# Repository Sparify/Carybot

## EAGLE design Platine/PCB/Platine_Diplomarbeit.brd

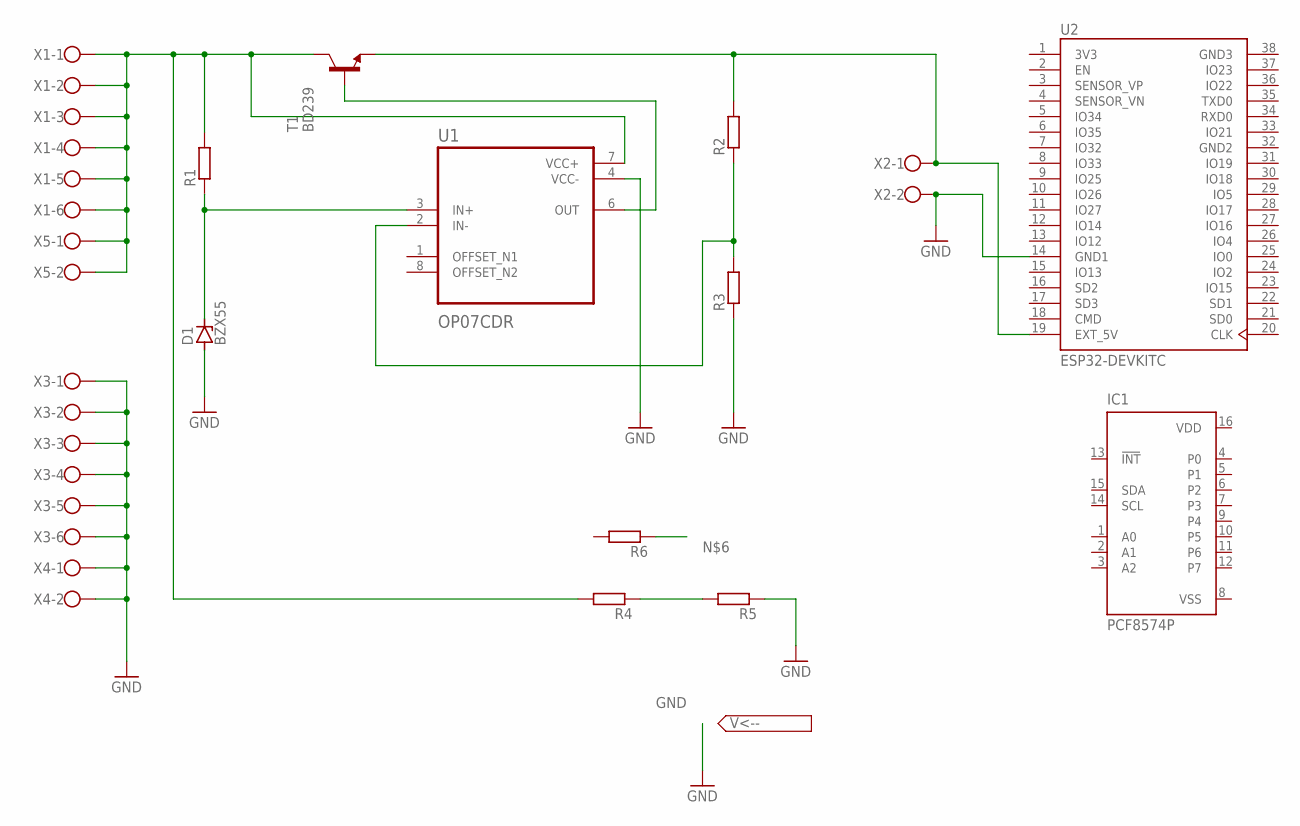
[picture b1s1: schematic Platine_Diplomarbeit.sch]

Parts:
D1: BZX55; DO35Z10
IC1: PCF8574P; DIL16
R1, R2, R3, R4, R5, R6: R-EU_0309/12; 0309/12
T1: BD239; TO220
U1: OP07CDR; SOIC127P599X175-8N
U2: ESP32-DEVKITC; MODULE_ESP32-DEVKITC
X1, X3: W237-6
X2, X4, X5: W237-102

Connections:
3V3: U2.1 (3V3)
GND: D1.A, R3.1, R5.1, U1.4 (VCC-), U2.14 (GND1), X2.2, X3.1, X3.2, X3.3, X3.4, X3.5, X3.6, X4.1, X4.2
GND1: R1.2, R4.2, T1.2 (C), U1.7 (VCC+), X1.1, X1.2, X1.3, X1.4, X1.5, X1.6, X5.1, X5.2
GND2: U2.32 (GND2)
GND3: U2.38 (GND3)
unnamed: D1.C, R1.1, U1.3 (IN+)
unnamed: R4.1, R5.2
unnamed: R2.2, T1.3 (E), U2.19 (EXT_5V), X2.1
unnamed: R2.1, R3.2, U1.2 (IN-)
unnamed: T1.1 (B), U1.6 (OUT)
VDD: IC1.16 (VDD)
VSS: IC1.8 (VSS)

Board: 2 copper layers, 16 parts (0 on the bottom side), 7 nets, no tracks yet.

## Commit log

2024-11-07 steuerung für 2 motoren
2024-11-07 Webserver files upload
2024-11-13 camera buttons + menu
2024-11-13 external files for js and css
2024-11-14 add 2nd site + cam_controll HTTPRequest + external files for css & js
2024-11-14 activate video stream
2024-11-14 add toggleable menu
2024-11-15 fixing body border
2024-11-20 change data from external site to menu
2024-11-21 remove RSSI & unused css
2024-12-06 Steuerungsoptimierung
2024-12-12 Change from HTTP to Websockets
2024-12-12 Webservercodeoptimierung
2024-12-19 Adding anti select + fixing cam control
2024-12-19 Codeoptimierung
2024-12-19 Codeoptimierungen
2024-12-28 Add files via upload
    v2
2024-12-28 Steuerung für 4 Motoren
2025-01-04 add connection status box
2025-01-04 fix control issue
2025-01-08 Spannungs_Messung
2025-01-09 distancesensor + spannungsmessung
2025-01-16 Akkustand auf webserver übertragen
2025-01-22 Change Host to ESP-CAM
2025-01-26 Videoübertragung über Websockets
2025-01-27 full websocket communication
2025-01-27 motorsteuerung implementieren
2025-01-27 improve fps + akkustand übertragen
2025-01-27 eigenes netzwerk carybot
2025-01-29 HX711_implemented
2025-01-29 pins_fuer_hx711_geaaendert
2025-01-30 optimierung
2025-01-30 camera control as slider
2025-01-30 Camera_movement_hinzugefuegt
2025-01-30 fix servo
2025-02-05 light_switch
2025-02-05 add fernlicht
2025-02-05 light_fix
2025-02-05 fix fernlicht
2025-02-06 fernlicht zustands toggle
2025-02-06 mcp_motor_test
2025-02-06 motor_auf_mcp
2025-02-06 battery_fixed
2025-02-06 distance_measuring
2025-02-21 LaTex_ordner
    jetzt erstmal LaTex fetzen
2025-02-21 titel_seite
    latex is voll geil
2025-02-21 eidesstattliche erklaerung
    nach dem vorbild des bildungsministeriums
2025-02-21 danksagung plus inhaltsverzeichnis
    In LaTex macht schreiben so viel Spass
2025-02-21 einleitung_zusammenfassung_abstract
2025-02-21 paket fuer namen in fusszeile eingefuegt und als muster benutzt
2025-02-24 Unterkapitel
2025-02-24 Inhalstverzeichnis
2025-02-26 abstandssensor_integriert
2025-02-26 Motoren gefixt
2025-02-27 Inhaltsverzeichnis updated
2025-02-27 updated 2.0
2025-02-27 Add content
    Schriftgröße 12
    1.5 Zeilenabstand
    Times New Roman
    -Grundlegende Ziele
    -SPIFFS Setup
    -VS-Code
2025-02-28 add content
    -webserver setup
    -kommunkation setup
    -message handling
    -kamera setup
    -videoübertragung
2025-03-02 projektteam und meilensteine hinzugefuegt
    latex is einfach beschte
2025-03-02 kostenaufstellung hinzugefuegt
2025-03-02 upload content
    -Steuerkreuz
    -Geschwindigkeitseinstellung
    -Kamerasteuerung
    -Echtzeit-Videoanzeige
    -Sensordaten
    -Verbindungsstatus
2025-03-03 upload content
    -fernlicht
2025-03-03 make bilder schön für flex
2025-03-03 upload logo
2025-03-03 add pictures
2025-03-03 add images
2025-03-03 Dokumentation Antrieb
2025-03-04 upload images
2025-03-04 Dokumentation Inhalt dazu
2025-03-05 upload changes
2025-03-05 code geändert
2025-03-05 upload conetn
    images + optimierungen
2025-03-05 formatierung
2025-03-06 Projektplannung hinzugefügt
2025-03-06 add content + formatierung
2025-03-06 fixes
2025-03-06 bildbeschreibungen
2025-03-07 projektstrukturplan fertigestellt
    latex beste
2025-03-07 Dokumentation erweitert
2025-03-08 Kleinen Fehler bei Latex datei gefixt und bei main.cpp unötige Kommentare entfernt
2025-03-08 Antrieb erweiterung
2025-03-10 code_antrieb_content
2025-03-10 motoren_code fertiggestellt
2025-03-12 bibliothek beschreibungen hinzugefügt
2025-03-12 literaturverzeichnis
2025-03-12 fix wir
2025-03-12 fehler behoben eides erklärung
2025-03-12 bild
2025-03-12 gehäuse part für felix
2025-03-12 kleine Änderung
2025-03-12 Sensoren_hcsr04_hinzugefügt
2025-03-13 Änderungen von Feedback
2025-03-13 verbesserungen
2025-03-13 baumörtl fehler behoben
2025-03-15 sensoren gewichtsmessung hinzugefügt
2025-03-16 Werk-Vormörtel Änderungen umgesetzt
2025-03-16 unnötige Kapitel entfernen
2025-03-16 flex sein teil
2025-03-17 Realisierung + Materialliste
2025-03-17 wichtige änderungen
2025-03-19 bilder_hinzugefügt
2025-03-19 esp32 inhalt hinzugefügt
2025-03-19 sg90 servomotor inhalt hinzugefügt
2025-03-20 bild hinzugefügt
2025-03-20 büld
2025-03-20 hardwaredesinge
2025-03-20 schavi - servo
2025-03-20 anpassungen
2025-03-23 korektur
2025-03-29 spannungsmessung hinzugefügt
2025-03-29 servo inhalt fertiggestellt
2025-03-29 add github description
2025-03-29 add link
2025-03-30 erweiterung des gehäuses
2025-03-31 sdsd
2025-03-31 latex beschreibung hinzugefügt
2025-03-31 lichtsteuerung hinzugefügt
2025-03-31 plan geupdatet
2025-04-03 bleibt jetzt stehn wenn abruch
2025-04-03 stop jetzt aber wirklich (Spielzeug)
2025-04-03 vs-code verbessert
2025-04-03 fixed code
2025-04-11 fertige version
2025-04-12 kamera gefixt und gewicht in kg
2025-04-22 feedback eingearbeitet
2025-04-30 fertig korrigierte diplomarbeit
